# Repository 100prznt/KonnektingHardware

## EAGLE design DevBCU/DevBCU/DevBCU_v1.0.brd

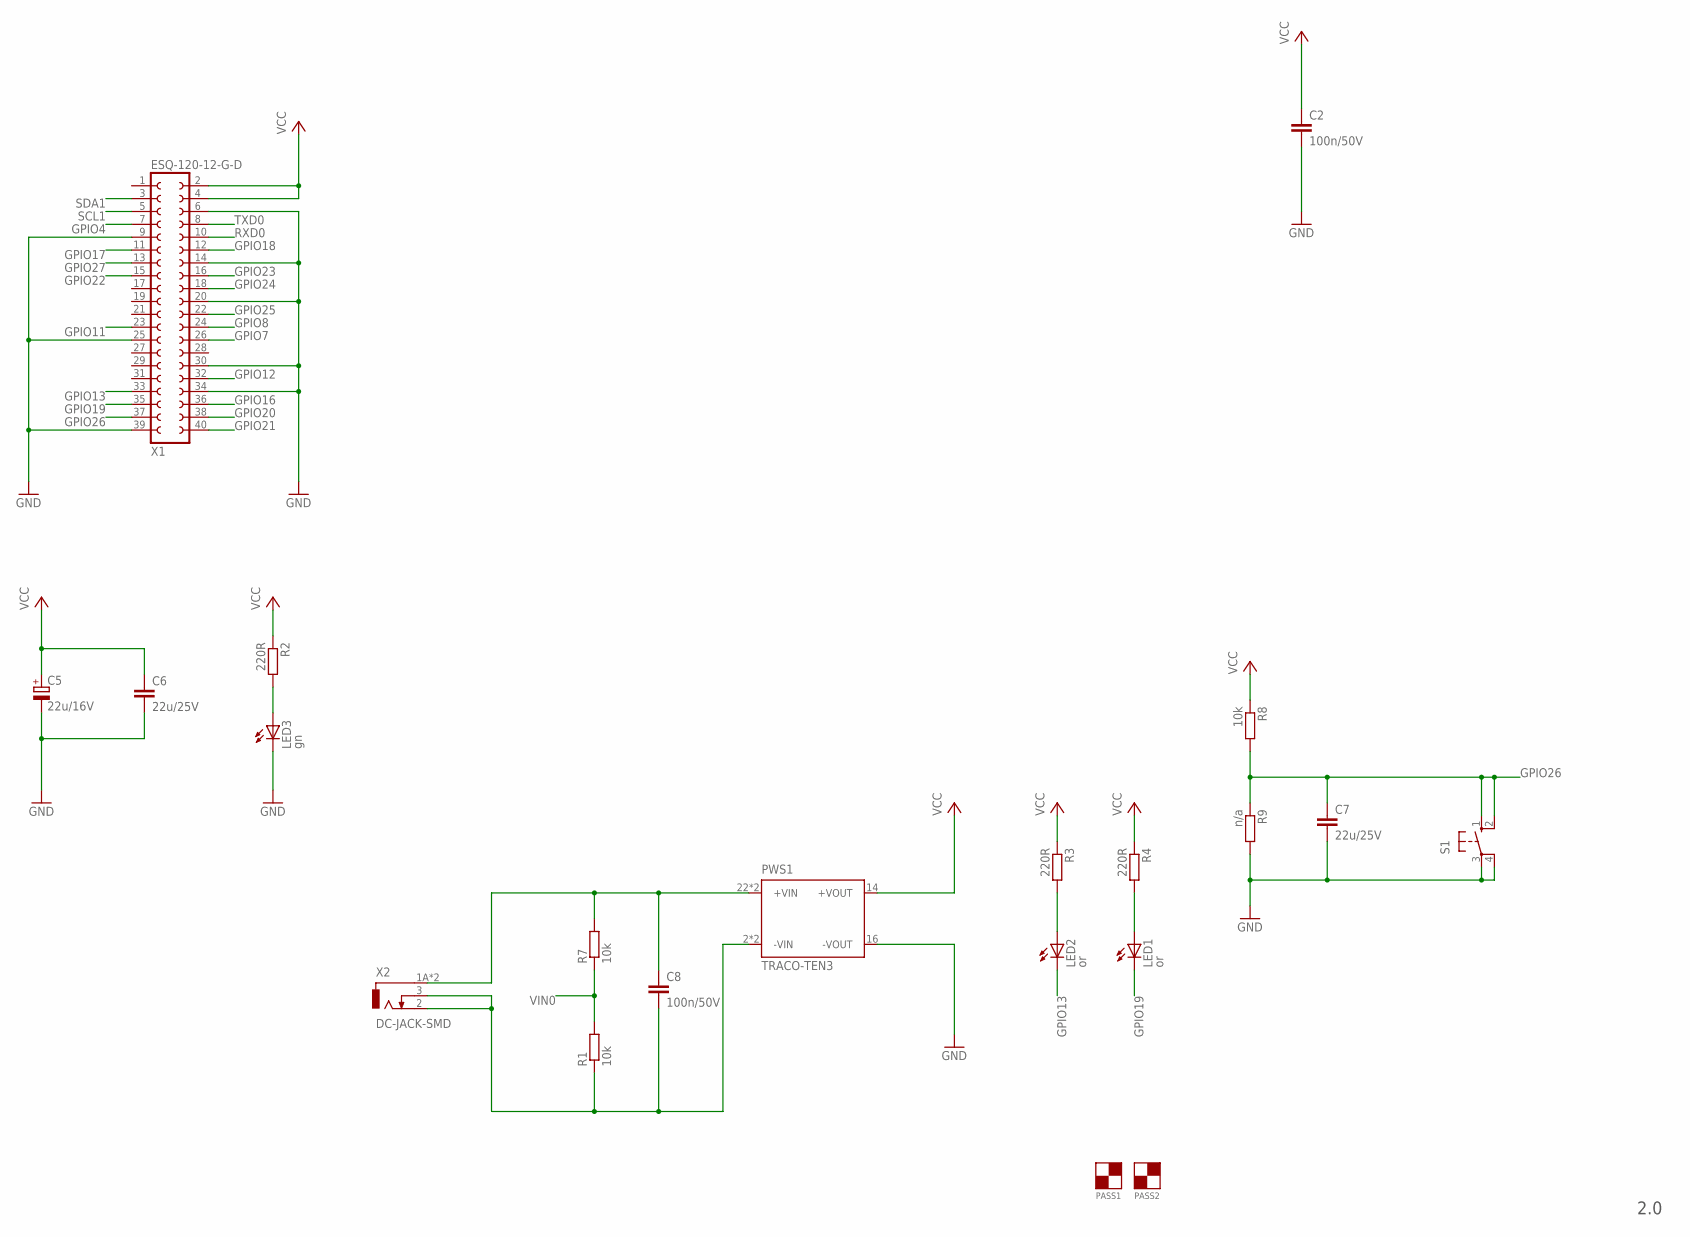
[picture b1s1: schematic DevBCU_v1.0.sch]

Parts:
C2, C8: 100n/50V; C0805
C5: 22u/16V; B/3528-21R
C6, C7: 22u/25V; C1210K
LED1, LED2: or; CHIP-LED0603
LED3: gn; CHIP-LED0603
PASS1, PASS2: MAKR1; MARK1
PWS1: TRACO-TEN3; TRACO_TEN_3
R1, R7: 10k; M0805
R2, R3, R4: 220R; R0805
R8: 10k; R0805
R9: n/a; R0805
S1: 10-XXS; B3FS-10XX
X1: ESQ-120-12-G-D; FE20-2
X2: DC-JACK-SMD; 694_1XX_106_102

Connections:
GND: C2.2, C5.-, C6.2, C7.2, LED3.C, PWS1.16 (-VOUT), R9.2, S1.3, S1.4 (P1), X1.6, X1.9, X1.14, X1.20, X1.25, X1.30, X1.34, X1.39
GPIO4: X1.7
GPIO7: X1.26
GPIO8: X1.24
GPIO11: X1.23
GPIO12: X1.32
GPIO13: LED2.C, X1.33
GPIO16: X1.36
GPIO17: X1.11
GPIO18: X1.12
GPIO19: LED1.C, X1.35
GPIO20: X1.38
GPIO21: X1.40
GPIO22: X1.15
GPIO23: X1.16
GPIO24: X1.18
GPIO25: X1.22
GPIO26: C7.1, R8.2, R9.1, S1.1 (S), S1.2 (S1), X1.37
GPIO27: X1.13
unnamed: LED3.A, R2.2
unnamed: LED2.A, R3.2
unnamed: LED1.A, R4.2
unnamed: C8.1, PWS1.22 (+VIN), PWS1.23 (+VIN), R7.2, X2.1A (1), X2.1B (1)
unnamed: C8.2, PWS1.2 (-VIN), PWS1.3 (-VIN), R1.1, X2.2, X2.3
RXD0: X1.10
SCL1: X1.5
SDA1: X1.3
TXD0: X1.8
VCC: C2.1, C5.+, C6.1, PWS1.14 (+VOUT), R2.1, R3.1, R4.1, R8.1, X1.2, X1.4
VIN0: R1.2, R7.1

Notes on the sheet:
2.0

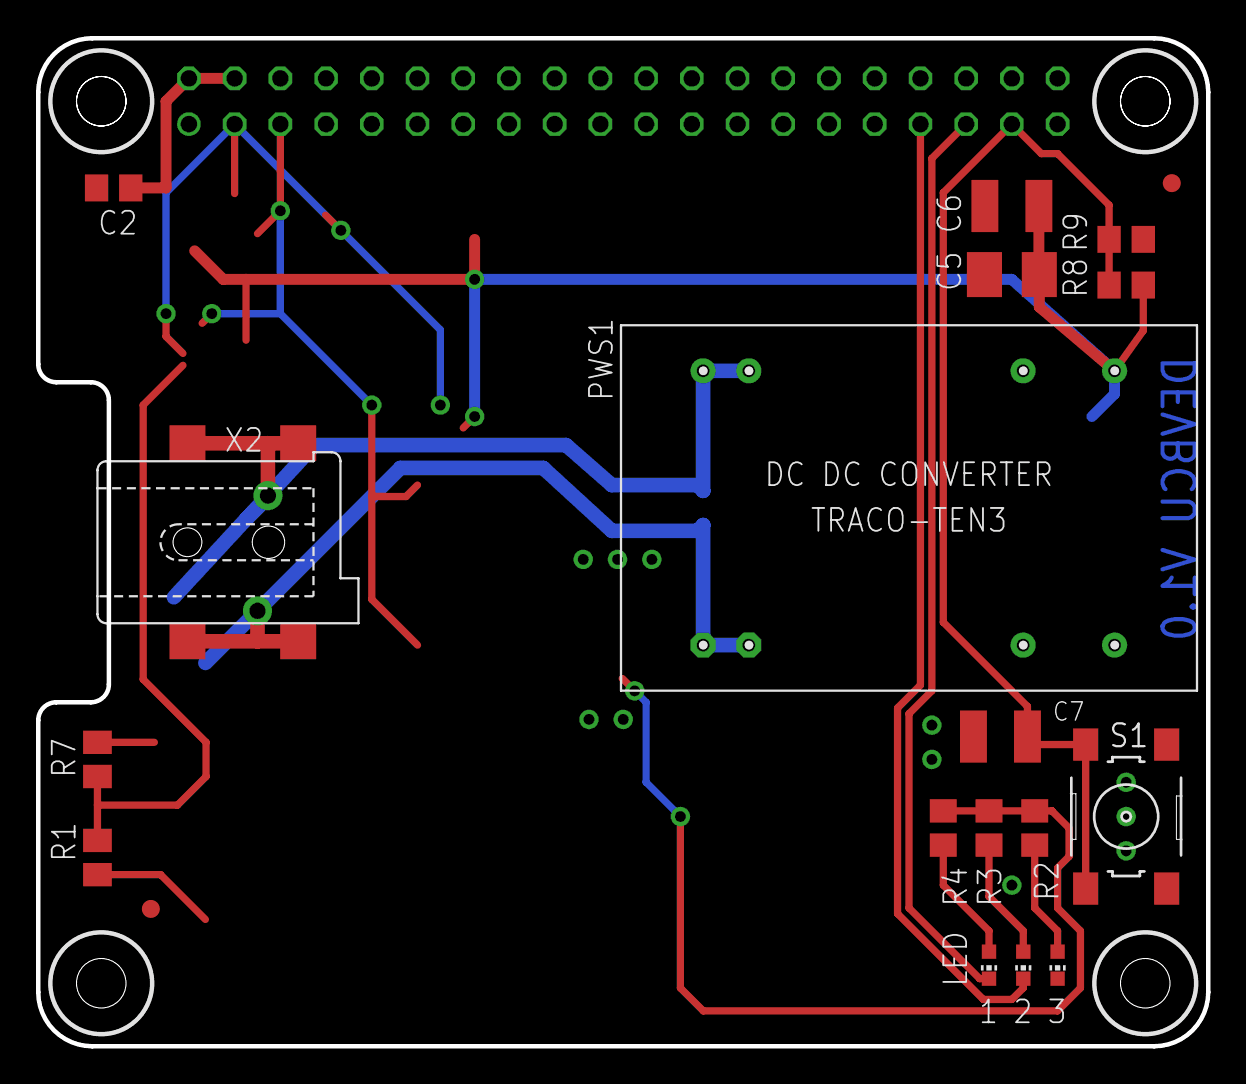
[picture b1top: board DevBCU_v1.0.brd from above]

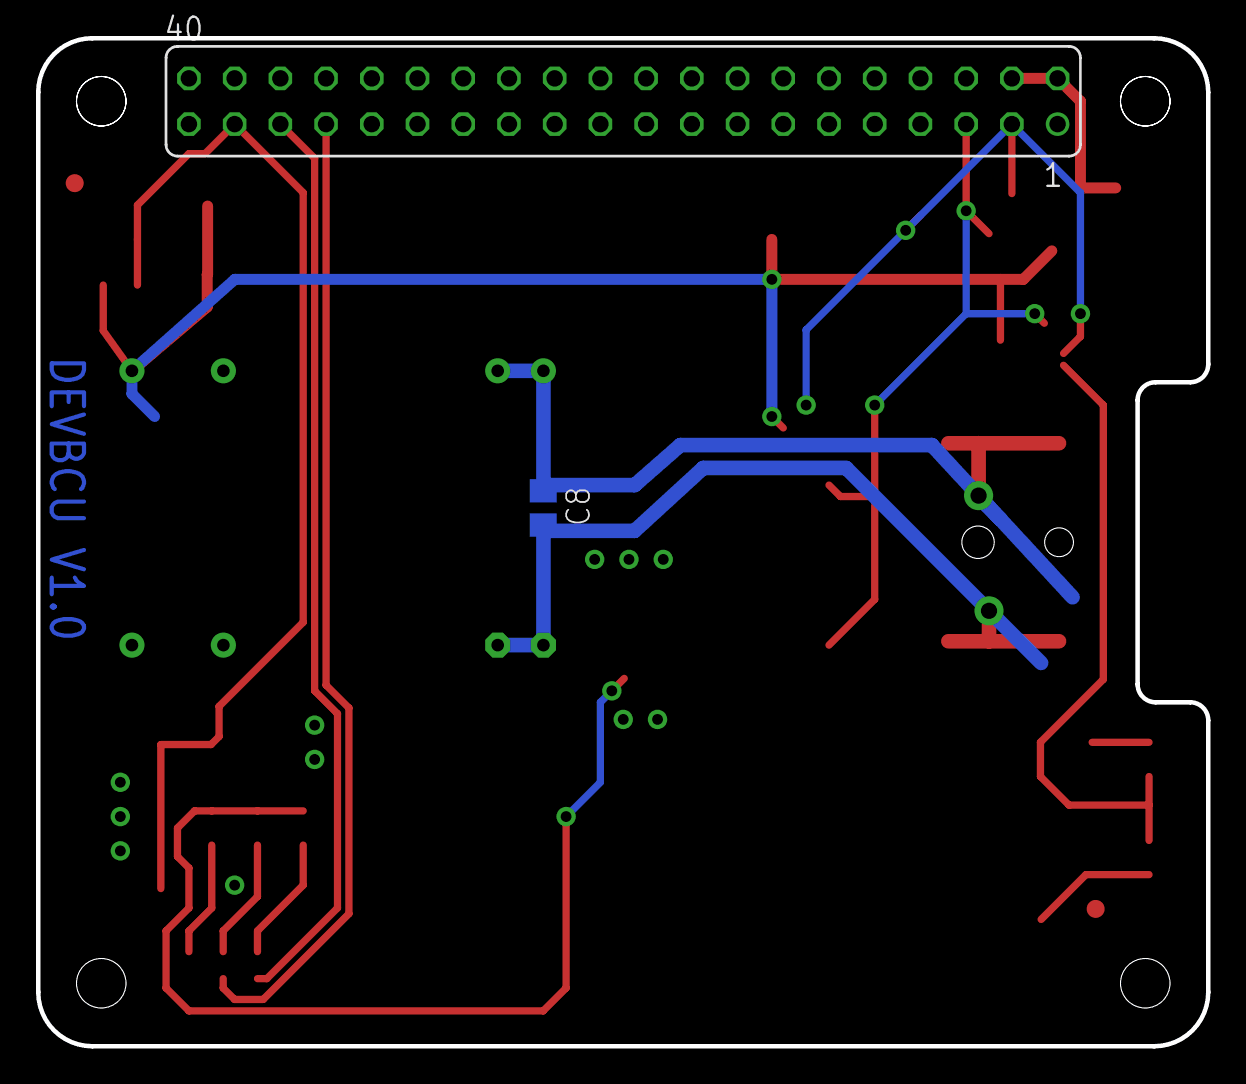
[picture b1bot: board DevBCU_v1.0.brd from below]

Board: 2 copper layers, 65.0 x 56.0 mm, 21 parts (2 on the bottom side), 11 nets.

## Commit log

2019-11-26 Add KNX Library (rca-knx.lbr)
    This library contains transceivers and components typically used in KNX (KNX TP1-256) compatible designs.
2019-11-26 Clean up
2019-11-26 Update libs
